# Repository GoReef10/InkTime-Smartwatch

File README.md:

# InkTime Smartwatch Project

InkTime is an open source startup focused on developing an affordable and customizable smartwatch centered around the nRF52840 SoC and e-ink display technology. This repository contains the full hardware design, including the schematic, PCB layout, and mechanical integration files required for mass production.

## Component Block Diagram

## Bill of Materials

| Device | Value | Qty | Parts | Product Link | Datasheet Link |
| --- | --- | --: | --- | --- | --- |
| NORDIC_NRF_4_NRF52840_QF | nRF52840-QIAA | 1 | U1 | [JLCPCB](https://jlcpcb.com/partdetail/NordicSemicon-NRF52840_QIAAR/C190794) | [Datasheet](https://infocenter.nordicsemi.com/pdf/nRF52840_PS_v1.9.pdf) |
| RT6160AWSC | RT6160AWSC | 1 | IC9 | [JLCPCB](https://jlcpcb.com/partdetail/RichtekTech-RT6160AWSC/C7065276) | [Datasheet](https://www.mouser.com/datasheet/2/1458/DS6160A_03-3104604.pdf) |
| BQ25180YBGR | BQ25180YBGR | 1 | IC1 | [JLCPCB](https://jlcpcb.com/partdetail/TexasInstruments-BQ25180YBGR/C3682423) | [Datasheet](https://www.ti.com/lit/ds/symlink/bq25180.pdf) |
| ESP32_C6_LIBRARY_MAX17048G+T10 | MAX17048G+T10 | 1 | U3 | [JLCPCB](https://jlcpcb.com/partdetail/MaximIntegrated-MAX17048GT10/C2682616) | [Datasheet](https://www.analog.com/media/en/technical-documentation/data-sheets/MAX17048-MAX17049.pdf) |
| DRV2605YZFR | DRV2605YZFR | 1 | IC2 | [JLCPCB](https://jlcpcb.com/partdetail/TexasInstruments-DRV2605YZFR/C81079) | [Datasheet](https://www.ti.com/lit/ds/symlink/drv2605.pdf) |
| BMA421 | BMA421 | 1 | IC3 | [JLCPCB](https://jlcpcb.com/partdetail/BoschSensortec-BMA421/C5242966) | [Datasheet](https://files.pine64.org/doc/datasheet/pinetime/BST-BMA421-FL000.pdf) |
| DMG2305UX-7 | DMG2305UX-7 | 1 | Q2 | [JLCPCB](https://jlcpcb.com/partdetail/HXYMOSFET-DMG2305UX7/C5261054) | [Datasheet](https://www.diodes.com/assets/Datasheets/DMG2305UX.pdf) |
| ESP32_C6_LIBRARY_6_SI1308EDL-T1-GE3 | SI1308EDL-T1-GE3 | 1 | Q3 | [JLCPCB](https://jlcpcb.com/partdetail/TECHPUBLIC-SI1308EDL/C7603347) | [Datasheet](https://www.vishay.com/docs/63399/si1308edl.pdf) |
| USBLC6-2SC6Y | USBLC6-2SC6Y | 1 | D3 | [JLCPCB](https://jlcpcb.com/partdetail/TECHPUBLIC-USBLC62SC6Y/C5310974) | [Datasheet](https://wmsc.lcsc.com/wmsc/upload/file/pdf/v2/lcsc/2401261525_TECH-PUBLIC-USBLC6-2SC6Y_C5310974.pdf) |
| MBR0530 | MBR0530 | 3 | D2, D4, D5 | [JLCPCB](https://jlcpcb.com/partdetail/4324765-MBR0530_F20000HF/C3757235) | [Datasheet](https://wmsc.lcsc.com/wmsc/upload/file/pdf/v2/lcsc/2205311800_Yangzhou-Yangjie-Electronic-Technology-MBR0530-F2-0000HF_C3757235.pdf) |
| KH-TYPE-C-16P_KH-TYPE-C-16P | KH-TYPE-C-16P | 1 | J4 | [JLCPCB](https://jlcpcb.com/partdetail/KH-TYPE-C-16P/C709357) | [Datasheet](https://wmsc.lcsc.com/wmsc/upload/file/pdf/v2/lcsc/2204251630_SHENZHEN-KINGHELM-Elec-KH-TYPE-C-16P_C709357.pdf) |
| 5034802400 | 503480-2400 | 1 | J1 | [JLCPCB](https://jlcpcb.com/partdetail/MOLEX-5034802400/C122434) | [Datasheet](https://www.mouser.com/datasheet/2/276/2/5034802400_FFC_FPC_CONNECTORS-1112921.pdf) |
| EVP-AKE31A | EVP-AKE31A | 3 | SW_DN, SW_ENT, SW_UP | [JLCPCB](https://jlcpcb.com/partdetail/PANASONIC-EVPAKE31A/C569760) | [Datasheet](https://www.lcsc.com/datasheet/C569760.pdf) |
| 2450AT18B100E_2450AT18B100E | 2450AT18B100E | 1 | ANT1 | [JLCPCB](https://jlcpcb.com/partdetail/JohansonTechnology-2450AT18B100/C2836414) | [Datasheet](https://www.johansontechnology.com/datasheets/antennas/2450AT18B100.pdf) |
| NX2016SA-32MHZ-STD-CZS-5 | 32 MHz | 1 | X1 | [JLCPCB](https://jlcpcb.com/partdetail/NDK-NX2016SA_32MHZ_STD_CZS5/C843260) | [Datasheet](https://www.lcsc.com/datasheet/C843260.pdf) |
| NORDIC_NRF_1_XTAL_32KHZ | 32.768 kHz | 1 | X2 | [JLCPCB](https://jlcpcb.com/partdetail/NDK-NX3215SA_32_768K_STD_MUA9/C519280) | [Datasheet](https://www.ndk.com/images/products/crystal/resonator/NX3215SA_e.pdf) |
| MLP2016SR47MT0S1_FTC252012SR47MBCA | FTC252012SR47MBCA | 1 | L7 | [JLCPCB](https://jlcpcb.com/partdetail/6763488-FTC252012SR47MBCA/C5832368) | [Datasheet](https://wmsc.lcsc.com/wmsc/upload/file/pdf/v2/lcsc/2311271530_TDK-FTC252012SR47MBCA_C5832368.pdf) |
| VHF060303H3N9ST | 3.9 nH | 1 | L1 | [JLCPCB](https://jlcpcb.com/partdetail/153834-VHF060303H3N9ST/C142503) | [Datasheet](https://www.lcsc.com/datasheet/C142503.pdf) |
| MLK0603L15NJT000 | 15 nH | 1 | L3 | [JLCPCB](https://jlcpcb.com/partdetail/TDK-MLK0603L15NJT000/C6990407) | [Datasheet](https://www.lcsc.com/datasheet/C6990407.pdf) |
| RNCF0201DTC3K30 | 3.3 kΩ | 2 | R17, R18 | [JLCPCB](https://jlcpcb.com/partdetail/SEI_Stackpole_Elec-RNCF0201DTC3K30/C2487997) | [Datasheet](https://www.lcsc.com/datasheet/C2487997.pdf) |
| RC0201FR-075K1L | 5.1 kΩ | 2 | R1_USB, R2_USB | [JLCPCB](https://jlcpcb.com/partdetail/YAGEO-RC0201FR075K1L/C274341) | [Datasheet](https://www.lcsc.com/datasheet/C274341.pdf) |
| RC0201FR-1310KL | 10 kΩ | 6 | R2_EP_DR, R5, R7, R8, R9, R_PWR_EPD | [JLCPCB](https://jlcpcb.com/partdetail/YAGEO-RC0201FR1310KL/C6373588) | [Datasheet](https://www.lcsc.com/datasheet/C6373588.pdf) |
| 0201WMF220KTCE | 2.2 Ω | 1 | R_TYPE_SEL | [JLCPCB](https://jlcpcb.com/partdetail/244650-0201WMF220KTCE/C247442) | [Datasheet](https://www.lcsc.com/datasheet/C247442.pdf) |
| 0201WMJ0000TCE | 0 Ω | 3 | R2, R3, R4 | [JLCPCB](https://jlcpcb.com/partdetail/25793-0201WMJ0000TCE/C25050) | [Datasheet](https://www.lcsc.com/datasheet/C25050.pdf) |
| MA0201XF821K250 | 820 pF | 1 | C9 | [JLCPCB](https://jlcpcb.com/partdetail/Meritek-MA0201XF821K250/C3842403) | [Datasheet](https://www.lcsc.com/datasheet/C3842403.pdf) |
| GRM0335C1E1R0CA01J | 1 pF | 2 | C3, C4 | [JLCPCB](https://jlcpcb.com/partdetail/2274979-GRM0335C1E1R0CA01J/C2182912) | [Datasheet](https://www.lcsc.com/datasheet/C2182912.pdf) |
| 0201N120J250CT | 12 pF | 4 | C1, C2, C17, C18 | [JLCPCB](https://jlcpcb.com/partdetail/Walsin_TechCorp-0201N120J250CT/C424835) | [Datasheet](https://www.lcsc.com/datasheet/C424835.pdf) |
| 0201N101F160CT | 100 pF | 1 | C11 | [JLCPCB](https://jlcpcb.com/partdetail/Walsin_TechCorp-0201N101F160CT/C3847857) | [Datasheet](https://www.lcsc.com/datasheet/C3847857.pdf) |
| C0201X5R473K160NTA | 47 nF | 1 | C16 | [JLCPCB](https://jlcpcb.com/partdetail/126083-C0201X5R473K160NTA/C124806) | [Datasheet](https://www.lcsc.com/datasheet/C124806.pdf) |
| AC0201KRX6S6BB104 | 100 nF | 9 | C5, C7, C8, C12, C19, C23, C27, C34, C42 | [JLCPCB](https://jlcpcb.com/partdetail/YAGEO-AC0201KRX6S6BB104/C3855913) | [Datasheet](https://www.lcsc.com/datasheet/C3855913.pdf) |
| CL05A105KP5NNNC | 1 uF | 1 | C15 | [JLCPCB](https://jlcpcb.com/partdetail/C14445) | [Datasheet](https://www.lcsc.com/datasheet/C14445.pdf) |
| GRM155R61H105KE05D | 1 uF / 50V | 9 | EPD_C1, EPD_C2, EPD_C6, EPD_C7, EPD_C8, EPD_C9, EPD_C10, EPD_C11, EPD_C12 | [JLCPCB](https://jlcpcb.com/partdetail/1609005-GRM155R61H105KE05D/C1518208) | [Datasheet](https://www.lcsc.com/datasheet/C1518208.pdf) |
| GRM155R61A475KEAAD | 4.7 uF | 5 | C6, C14, C20, C21, C43 | [JLCPCB](https://jlcpcb.com/partdetail/MurataElectronics-GRM155R61A475KEAAD/C77004) | [Datasheet](https://www.lcsc.com/datasheet/C77004.pdf) |
| C0402X5R475M250NT | 4.7 uF / 25V | 1 | C2-EP-DR | [JLCPCB](https://jlcpcb.com/partdetail/SANYEAR-C0402X5R475M250NT/C2911388) | [Datasheet](https://www.lcsc.com/datasheet/C2911388.pdf) |
| 0402X106M100CT | 10 uF | 2 | C24, C39 | [JLCPCB](https://jlcpcb.com/partdetail/Walsin_TechCorp-0402X106M100CT/C2992625) | [Datasheet](https://www.lcsc.com/datasheet/C2992625.pdf) |
| CL05A226MQ6ZUN8 | 22 uF | 2 | C25, C33 | [JLCPCB](https://jlcpcb.com/partdetail/2889851-CL05A226MQ6ZUN8/C2762589) | [Datasheet](https://www.lcsc.com/datasheet/C2762589.pdf) |

## Hardware Description

### Microcontroller - nRF52840 (Nordic Semiconductor)

The core of InkTime is the **nRF52840**. It manages all peripherals and runs the main firmware:

### Power System

- **LiPo Charger - BQ25180YBGR :** Single-cell Li-Ion/LiPo charger connected via **I2C**, handles charge current control and power path management.
- **DC/DC Buck-Boost - RT6160AWSC:** Provides the regulated **3.3 V rail** (VREG/3V3) from the battery, using a 10 uH inductor. Supplies the MCU and most peripherals.
- **Fuel Gauge - MAX17048G+T10:** Monitors battery state-of-charge via **I2C**, provides a `ALERT` line to the MCU for low-battery interrupts.

### E-Paper Display

The display connects through a 24-pin FPC connector (J1). The drive circuit uses:
- A boost converter to generate the higher voltages required by e-paper panels (PREVGH/PREVGL rails).
- Communication with the MCU via SPI (MOSI, SCK, CS, DC, RST, BUSY lines).

E-paper was chosen for its near-zero power draw when the display is static - only consuming power during refresh.

### IMU - BMA421

A 3-axis accelerometer connected via I2C, with two interrupt lines (`INT1`, `INT2`) wired to the MCU for step counting, wrist-tilt detection, and activity recognition without polling.

### Haptic Driver - DRV2605YZFR

Controls a vibration motor/LRA actuator. Connected via **I2C**, with an enable line (`HAPTIC_EN`) from the MCU. Supports waveform libraries for rich haptic feedback patterns.

### USB - KH-TYPE-C-16P + USBLC6-2SC6Y

Full-speed USB Type-C connector for charging and data. The USBLC6-2SC6Y provides ESD protection on D+/D− lines. CC1/CC2 resistors (5.1 kΩ) handle cable orientation detection. VBUS is routed to the LiPo charger.

### Buttons

Three tactile buttons (UP, DOWN, ENTER) with pull-up resistors, directly connected to GPIO pins.

### Debug Interface - TC2030-IDC (Tag-Connect)

A 6-pin **SWD** debug/programming header (SWDCLK, SWDIO, RESET, SWO, 3.3V, GND) for firmware flashing and debugging, with test points exposed for each signal.

## nRF52840 Pin Assignment - InkTime v5

### SPI - E-Paper Display
| Pin | Function | Why |
|-----|----------|-----|
| P0.08 | MOSI | SPI data out to EPD controller |
| P0.11 | SCK | SPI clock |
| P0.13 | EPD_CS | Chip select - activates the display |
| P0.14 | EPD_DC | Data/Command toggle for EPD protocol |
| P1.01 | EPD_RST | Hardware reset of the display controller |
| P1.02 | EPD_BUSY | Polled input - MCU waits for display to finish refreshing |

### I2C - Shared Bus (BQ25180, MAX17048, BMA421, DRV2605)
| Pin | Function | Why |
|-----|----------|-----|
| P0.26 | SCL | I2C clock, shared by all 4 peripherals |
| P0.27 | SDA | I2C data, shared by all 4 peripherals |

### Interrupts & Control
| Pin | Function | Why |
|-----|----------|-----|
| P0.04 | PMIC_INT | BQ25180 interrupt - charge events (fault, complete, etc.) |
| P1.09 | ALERT | MAX17048 interrupt - low battery or 1% SoC change |
| P0.25 | IMU_INT1 | BMA421 primary interrupt - step count, wakeup-on-motion |
| P0.24 | IMU_INT2 | BMA421 secondary interrupt - activity recognition events |
| P1.01 | HAPTIC_EN | Enables DRV2605 and triggers haptic waveform playback |

### Buttons
| Pin | Function | Why |
|-----|----------|-----|
| P0.29 | SW_UP | Up button - GPIOTE falling-edge interrupt, also wakes MCU from sleep |
| P0.30 | SW_DN | Down button - same as above |
| P0.31 | SW_ENT | Enter button - same as above |

### USB
| Pin | Function | Why |
|-----|----------|-----|
| D+ | USB D+ | Native USB 2.0 FS controller - firmware updates, serial debug |
| D− | USB D− | Paired with D+ |
| VBUS | USB power detect | MCU detects cable insertion to enable charging path |

### Crystal Oscillators
| Pin | Function | Why |
|-----|----------|-----|
| XL1 / XL2 | 32.768 kHz XTAL | Low-frequency RTC clock - timekeeping during deep sleep |
| XC1 / XC2 | 32 MHz XTAL | Main system clock for CPU and radio |

### SWD Debug
| Pin | Function | Why |
|-----|----------|-----|
| SWDCLK | SWD clock | Firmware flashing and live debugging via Tag-Connect |
| SWDIO | SWD data | Bidirectional debug data |
| P1.00 | SWO | Serial Wire Output - trace/printf during development |
| P0.18 | RESET | Hardware reset, also accessible on debug header |

### RF
| Pin | Function | Why |
|-----|----------|-----|
| ANT | 2.4 GHz antenna | Connected via LC matching network to the onboard ceramic antenna |
| VSS_PA | PA ground | Dedicated quiet ground for the RF power amplifier |

## Design Log

### Silkscreen
Silkscreen line width was set to **0.9 mm**, reduced to **0.8 mm** in areas where overlap with component courtyard or pad holes would otherwise occur. While the standard recommendation is 1 mm, 0.9 mm remains legible after fabrication. To reduce visual clutter, silkscreen labels were kept only for functionally important components (ICs, connectors, test points) - passive components such as resistors and capacitors were left unlabeled.

### Test Points
All test points (SWD signals, power rails, I2C lines) were placed close to the board edge to allow easy probing during bring-up and testing without needing to reach into the center of the board.

### Antenna Placement
The BLE antenna (2450AT18B100E) was placed at the edge of the PCB, away from other components and copper fills, to minimize RF interference and avoid detuning the antenna due to nearby conductors - a standard requirement for 2.4 GHz PCB antennas.

### Trace Width & Clearance
Power traces were routed at 0.3 mm as per design requirements. In a small number of cases, traces were temporarily narrowed immediately at component pins due to clearance constraints, then returned to 0.3 mm as soon as space allowed. This was done only where unavoidable and over very short distances, keeping the resistive impact negligible.

### 2-Layer Stackup
A 2-layer board (top + bottom copper) was chosen deliberately as the design complexity is manageable within 2 layers, so the added cost of additional layers would bring no practical benefit.

Power traces were routed on the top layer. The only exception is a short segment of the **3V3 trace** which briefly routes through the bottom layer through 3 vias, due to a localized routing constraint. This was kept to an absolute minimum, which is particularly important for noisy nets like the e-paper boost converter output.

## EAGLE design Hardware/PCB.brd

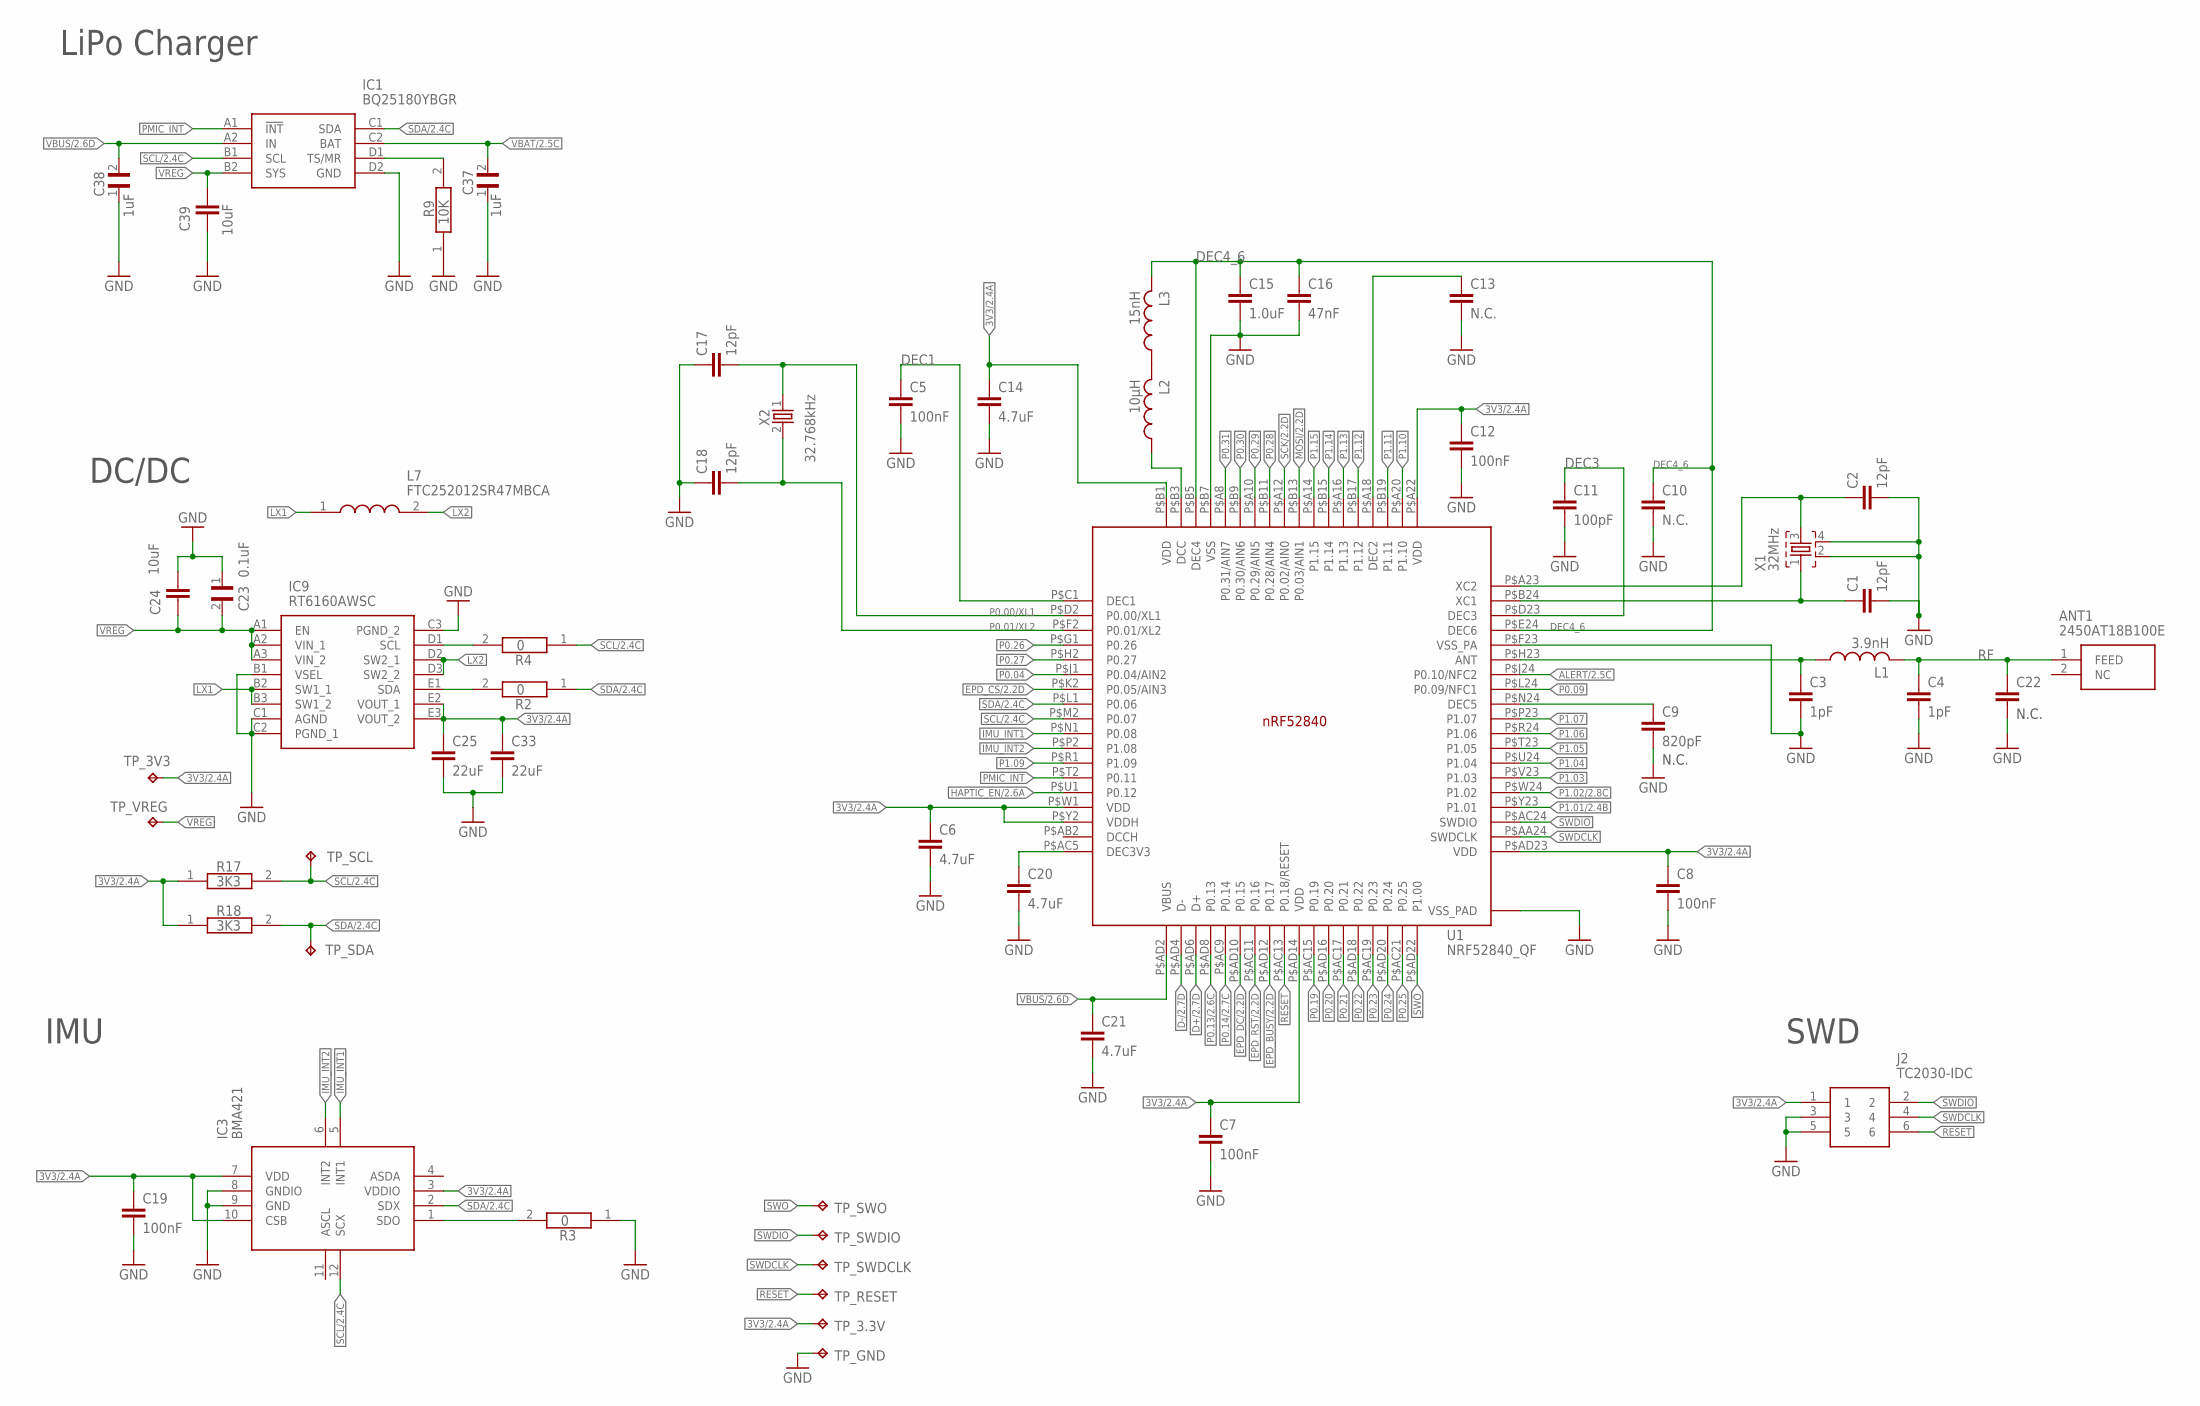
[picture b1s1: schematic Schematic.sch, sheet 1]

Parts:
ANT1: 2450AT18B100E; 2450AT18B100E_ANTC3216X140N
C1, C2, C17, C18: 12pF; NORDIC_NRF_3_RESC0201_L
C3, C4: 1pF; NORDIC_NRF_3_RESC0201_L
C5, C7, C8, C12, C19: 100nF; NORDIC_NRF_3_RESC0201_L
C6, C14, C20, C21: 4.7uF; NORDIC_NRF_3_RESC0402_L
C9: 820pF; NORDIC_NRF_3_RESC0201_L
C10, C13, C22: N.C.; NORDIC_NRF_3_RESC0201_L
C11: 100pF; NORDIC_NRF_3_RESC0201_L
C15: 1.0uF; NORDIC_NRF_3_RESC0402_L
C16: 47nF; NORDIC_NRF_3_RESC0201_L
C23: 0.1uF; GRM011R60J152KE01L_1_0201
C24, C39: 10uF; NORDIC_NRF_3_RESC0402_L
C25, C33: 22uF; NORDIC_NRF_3_RESC0402_L
C37, C38: 1uF; GRM011R60J152KE01L_1_0201
IC1: BQ25180YBGR; BQ25180YBGR_BGA8C40P2X4_100X155X50
IC3: BMA421; BMA423_BMA423
IC9: RT6160AWSC; RT6160AWSC_BGA15C40P3X5_140X230X60
J2: TC2030-IDC; TC2030-IDC_TC2030IDC
L1: 3.9nH; NORDIC_NRF_2_RESC0402_L
L2: 10μH; NORDIC_NRF_2_RESC0402_L
L3: 15nH; NORDIC_NRF_2_RESC0402_L
L7: FTC252012SR47MBCA; MLP2016SR47MT0S1_INDC2016X100N
R2, R3, R4: 0; ERA-1AEB3401C_0201
R9: 10K; ERA-1AEB3401C_0201
R17, R18: 3K3; ERA-1AEB3401C_0201
TP_3.3V, TP_3V3: HECTOR_WATCH_1_TPTP20R; HECTOR_WATCH_1_TP20R
TP_GND: HECTOR_WATCH_1_TPTP20R; HECTOR_WATCH_1_TP20R
TP_RESET: HECTOR_WATCH_1_TPTP20R; HECTOR_WATCH_1_TP20R
TP_SCL: HECTOR_WATCH_1_TPTP20R; HECTOR_WATCH_1_TP20R
TP_SDA: HECTOR_WATCH_1_TPTP20R; HECTOR_WATCH_1_TP20R
TP_SWDCLK: HECTOR_WATCH_1_TPTP20R; HECTOR_WATCH_1_TP20R
TP_SWDIO: HECTOR_WATCH_1_TPTP20R; HECTOR_WATCH_1_TP20R
TP_SWO: HECTOR_WATCH_1_TPTP20R; HECTOR_WATCH_1_TP20R
TP_VREG: HECTOR_WATCH_1_TPTP20R; HECTOR_WATCH_1_TP20R
U1: NRF52840_QF; NORDIC_NRF_4_AQFN50P700X700X85_HS-74N
X1: 32MHz; NORDIC_NRF_BT-XTAL_2016_N
X2: 32.768kHz; NORDIC_NRF_1_XTAL_3215_N

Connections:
3V3/2.4A: C6.1, C7.1, C8.1, C12.1, C14.1, C19.1, C25.1, C33.1, IC3.3 (VDDIO), IC3.7 (VDD), IC3.10 (CSB), IC9.E2 (VOUT_1), IC9.E3 (VOUT_2), J2.1, R17.1, R18.1, TP_3.3V.TP, TP_3V3.TP, U1.P$A22 (VDD), U1.P$AD14 (VDD), U1.P$AD23 (VDD), U1.P$B1 (VDD), U1.P$W1 (VDD), U1.P$Y2 (VDDH)
ALERT/2.5C: U1.P$J24 (P0.10/NFC2)
D+/2.7D: U1.P$AD6 (D+)
D-/2.7D: U1.P$AD4 (D-)
DEC1: C5.1, U1.P$C1 (DEC1)
DEC3: C11.1, U1.P$D23 (DEC3)
DEC4_6: C10.1, C15.1, C16.1, L3.2, U1.P$B5 (DEC4), U1.P$E24 (DEC6)
EPD_BUSY/2.2D: U1.P$AD12 (P0.17)
EPD_CS/2.2D: U1.P$K2 (P0.05/AIN3)
EPD_DC/2.2D: U1.P$AD10 (P0.15)
EPD_RST/2.2D: U1.P$AC11 (P0.16)
GND: C1.2, C2.2, C3.2, C4.2, C5.2, C6.2, C7.2, C8.2, C9.2, C10.2, C11.2, C12.2, C13.2, C14.2, C15.2, C16.2, C17.1, C18.1, C19.2, C20.2, C21.2, C22.2, C23.1, C24.1, C25.2, C33.2, C37.1, C38.1, C39.2, IC1.D2 (GND), IC3.8 (GNDIO), IC3.9 (GND), IC9.B1 (VSEL), IC9.C1 (AGND), IC9.C2 (PGND_1), IC9.C3 (PGND_2), J2.3, J2.5, R3.1, R9.1, TP_GND.TP, U1.P$74 (VSS_PAD), U1.P$75 (VSS_PAD), U1.P$76 (VSS_PAD), U1.P$77 (VSS_PAD), U1.P$78 (VSS_PAD), U1.P$79 (VSS_PAD), U1.P$80 (VSS_PAD), U1.P$81 (VSS_PAD), U1.P$82 (VSS_PAD), U1.P$83 (VSS_PAD), U1.P$84 (VSS_PAD), U1.P$85 (VSS_PAD), U1.P$86 (VSS_PAD), U1.P$87 (VSS_PAD), U1.P$88 (VSS_PAD), U1.P$89 (VSS_PAD), U1.P$90 (VSS_PAD), U1.P$B7 (VSS), U1.P$F23 (VSS_PA), X1.2, X1.4; also elsewhere on the board
HAPTIC_EN/2.6A: U1.P$U1 (P0.12)
IMU_INT1: IC3.5 (INT1), U1.P$N1 (P0.08)
IMU_INT2: IC3.6 (INT2), U1.P$P2 (P1.08)
LX1: IC9.B2 (SW1_1), IC9.B3 (SW1_2), L7.1
LX2: IC9.D2 (SW2_1), IC9.D3 (SW2_2), L7.2
MOSI/2.2D: U1.P$B13 (P0.03/AIN1)
unnamed: C20.1, U1.P$AC5 (DEC3V3)
unnamed: L2.2, L3.1
unnamed: L2.1, U1.P$B3 (DCC)
unnamed: C1.1, U1.P$B24 (XC1), X1.1
unnamed: C2.1, U1.P$A23 (XC2), X1.3
unnamed: IC9.E1 (SDA), R2.2
unnamed: IC9.D1 (SCL), R4.2
unnamed: IC1.D1 (TS/MR), R9.2
unnamed: C13.1, U1.P$A18 (DEC2)
unnamed: C9.1, U1.P$N24 (DEC5)
unnamed: IC3.1 (SDO), R3.2
unnamed: C3.1, L1.1, U1.P$H23 (ANT)
P0.00/XL1: C17.2, U1.P$D2 (P0.00/XL1), X2.1
P0.01/XL2: C18.2, U1.P$F2 (P0.01/XL2), X2.2
P0.04: U1.P$J1 (P0.04/AIN2)
P0.09: U1.P$L24 (P0.09/NFC1)
P0.13/2.6C: U1.P$AD8 (P0.13)
P0.14/2.7C: U1.P$AC9 (P0.14)
P0.19: U1.P$AC15 (P0.19)
P0.20: U1.P$AD16 (P0.20)
P0.21: U1.P$AC17 (P0.21)
P0.22: U1.P$AD18 (P0.22)
P0.23: U1.P$AC19 (P0.23)
P0.24: U1.P$AD20 (P0.24)
P0.25: U1.P$AC21 (P0.25)
P0.26: U1.P$G1 (P0.26)
P0.27: U1.P$H2 (P0.27)
P0.28: U1.P$B11 (P0.28/AIN4)
P0.29: U1.P$A10 (P0.29/AIN5)
P0.30: U1.P$B9 (P0.30/AIN6)
P0.31: U1.P$A8 (P0.31/AIN7)
P1.01/2.4B: U1.P$Y23 (P1.01)
P1.02/2.8C: U1.P$W24 (P1.02)
P1.03: U1.P$V23 (P1.03)
P1.04: U1.P$U24 (P1.04)
P1.05: U1.P$T23 (P1.05)
P1.06: U1.P$R24 (P1.06)
P1.07: U1.P$P23 (P1.07)
P1.09: U1.P$R1 (P1.09)
P1.10: U1.P$A20 (P1.10)
P1.11: U1.P$B19 (P1.11)
P1.12: U1.P$B17 (P1.12)
P1.13: U1.P$A16 (P1.13)
P1.14: U1.P$B15 (P1.14)
P1.15: U1.P$A14 (P1.15)
PMIC_INT: IC1.A1 (!INT), U1.P$T2 (P0.11)
RESET: J2.6, TP_RESET.TP, U1.P$AC13 (P0.18/RESET)
RF: ANT1.1 (FEED), C4.1, C22.1, L1.2
SCK/2.2D: U1.P$A12 (P0.02/AIN0)
SCL/2.4C: IC1.B1 (SCL), IC3.12 (SCX), R4.1, R17.2, TP_SCL.TP, U1.P$M2 (P0.07)
SDA/2.4C: IC1.C1 (SDA), IC3.2 (SDX), R2.1, R18.2, TP_SDA.TP, U1.P$L1 (P0.06)
SWDCLK: J2.4, TP_SWDCLK.TP, U1.P$AA24 (SWDCLK)
SWDIO: J2.2, TP_SWDIO.TP, U1.P$AC24 (SWDIO)
SWO: TP_SWO.TP, U1.P$AD22 (P1.00)
VBAT/2.5C: C37.2, IC1.C2 (BAT)
VBUS/2.6D: C21.1, C38.2, IC1.A2 (IN), U1.P$AD2 (VBUS)
VREG: C23.2, C24.2, C39.1, IC1.B2 (SYS), IC9.A1 (EN), IC9.A2 (VIN_1), IC9.A3 (VIN_2), TP_VREG.TP

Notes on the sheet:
LiPo Charger
DC/DC
IMU
SWD
N.C.

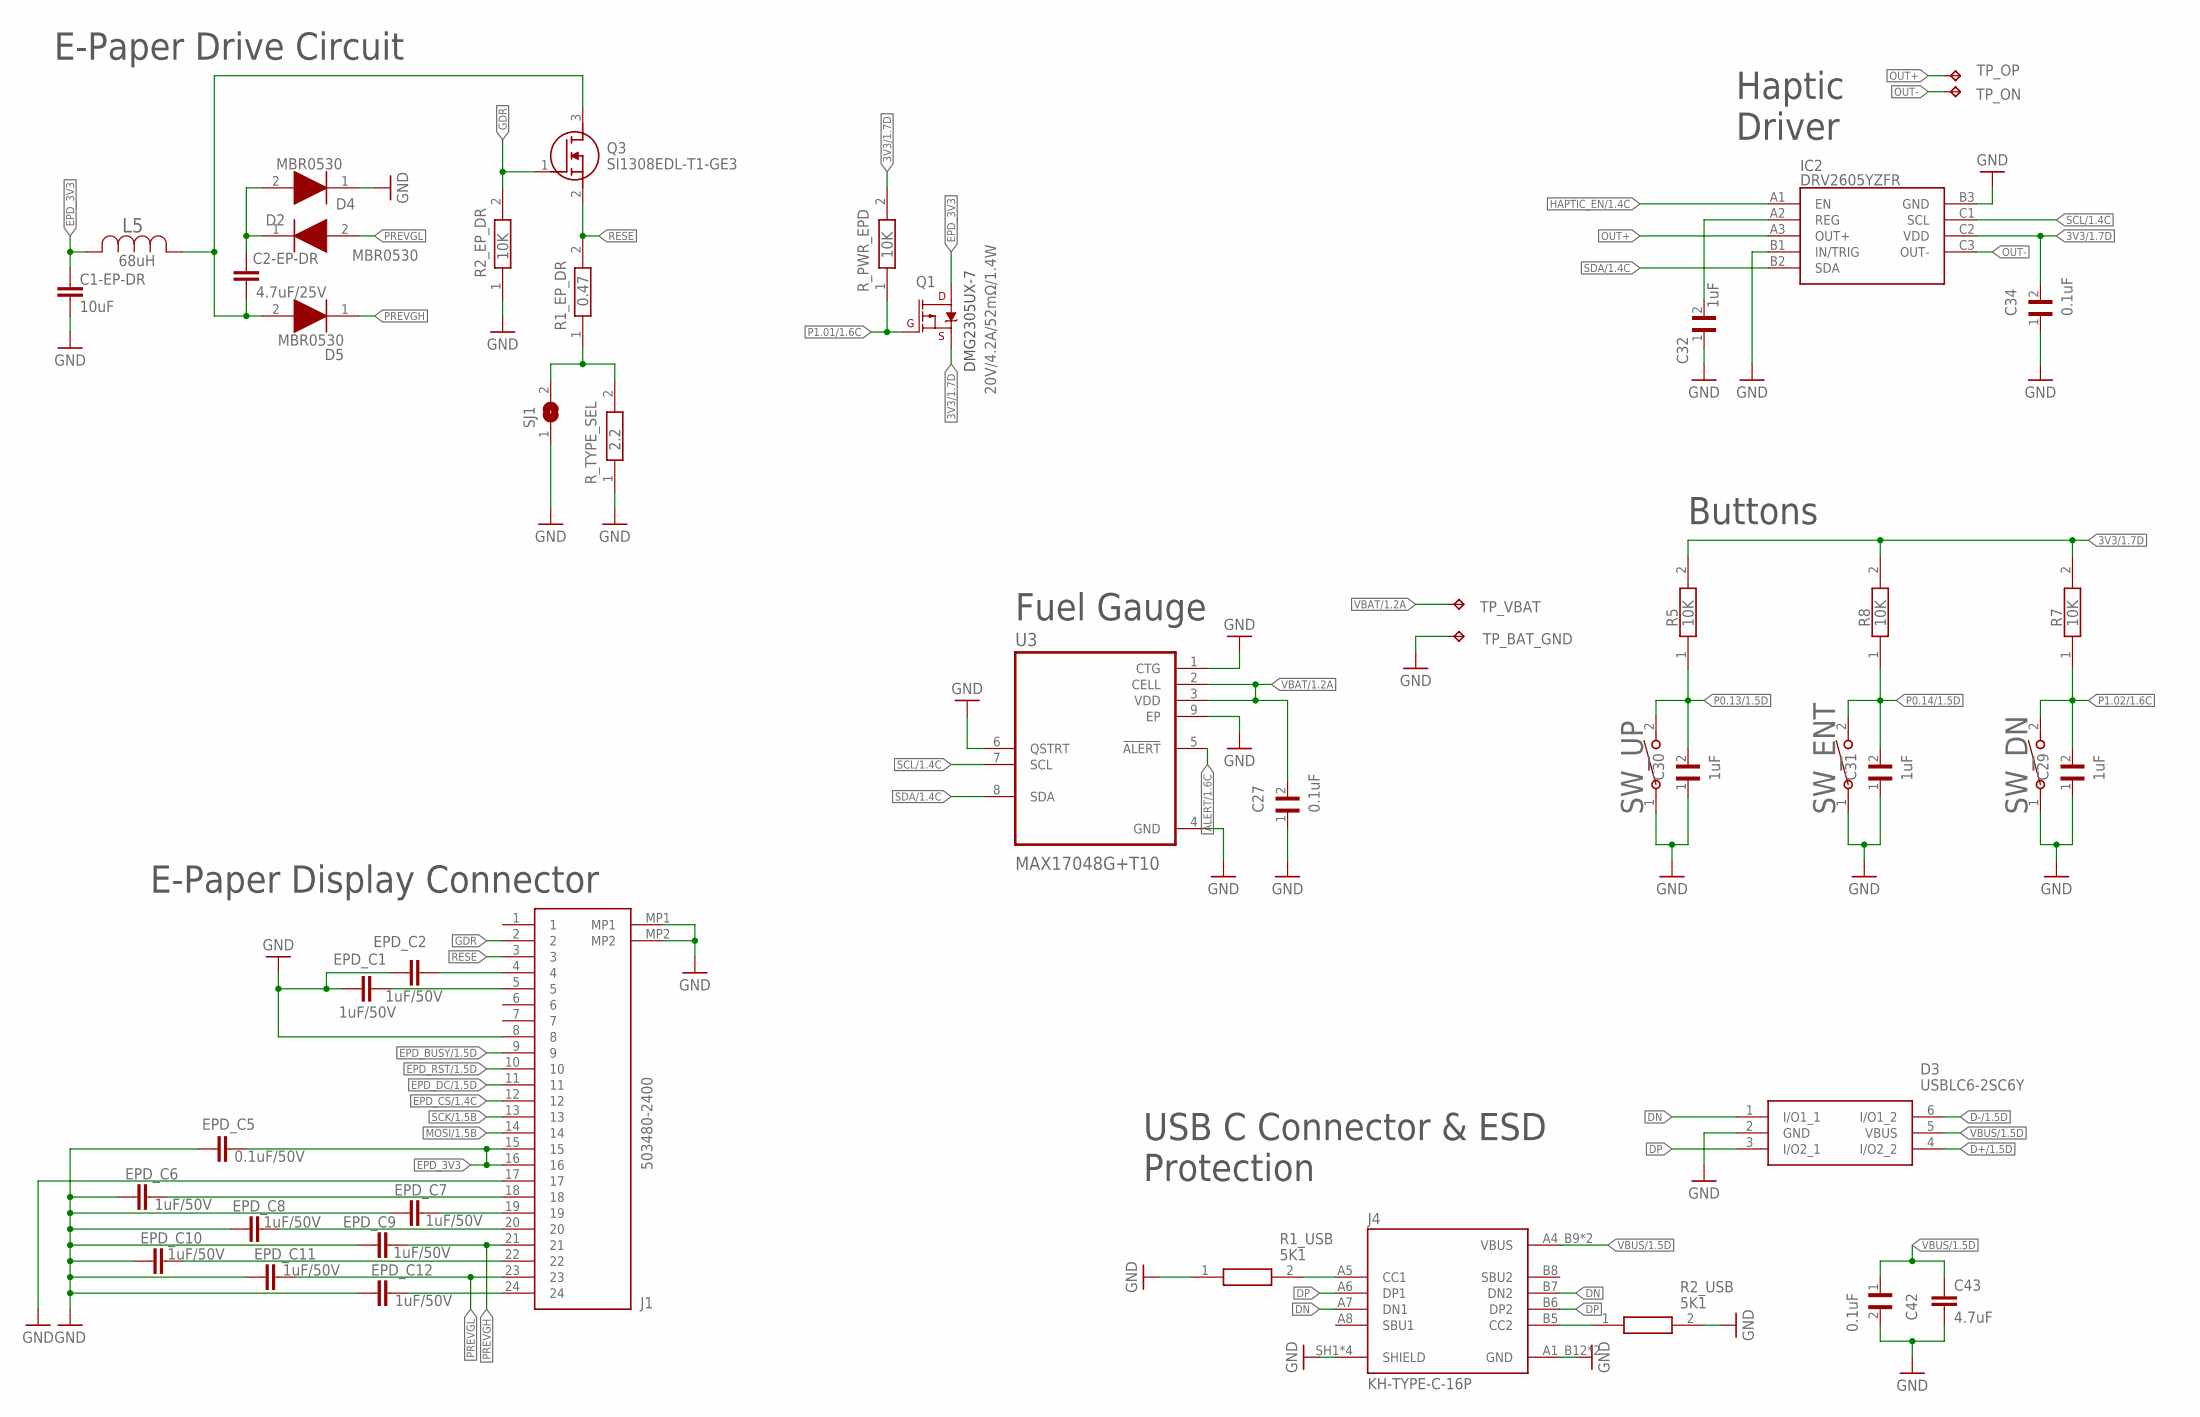
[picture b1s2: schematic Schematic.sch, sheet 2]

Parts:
C1-EP-DR: 10uF; NORDIC_NRF_3_RESC0402_L
C2-EP-DR: 4.7uF/25V; NORDIC_NRF_3_RESC0402_L
C27, C34, C42: 0.1uF; GRM011R60J152KE01L_1_0201
C29, C30, C31, C32: 1uF; GRM011R60J152KE01L_1_0201
C43: 4.7uF; NORDIC_NRF_3_RESC0402_L
D2, D4, D5: MBR0530; ESP32_C6_LIBRARY_5_SOD3716X135N
D3: USBLC6-2SC6Y; ESP32_C6_LIBRARY_3_SOT95P280X145-6N
EPD_C1, EPD_C2, EPD_C6, EPD_C7, EPD_C8, EPD_C9, EPD_C10, EPD_C11, EPD_C12: 1uF/50V; NORDIC_NRF_3_RESC0402_L
EPD_C5: 0.1uF/50V; NORDIC_NRF_3_RESC0201_L
IC2: DRV2605YZFR; DRV2605YZFR_BGA9C50P3X3_144X144X62
J1: 503480-2400; 503480-2400_5034802400
J4: KH-TYPE-C-16P; KH-TYPE-C-16P_KINGHELM_KH-TYPE-C-16P
L5: 68uH; ESP32_C6_LIBRARY_2_IND_4828-WE-TPC_WRE
Q1: 20V/4.2A/52mΩ/1.4W; ESP32_C6_LIBRARY_4_ESP32_C6_LIBRARY_4_ESP32_C6_LIBRARY_4_ES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
Q3: SI1308EDL-T1-GE3; ESP32_C6_LIBRARY_6_SOT65P210X110-3N
R1_EP_DR: 0.47; ERA-1AEB3401C_0201
R1_USB, R2_USB: 5K1; ERA-1AEB3401C_0201
R2_EP_DR, R5, R7, R8: 10K; ERA-1AEB3401C_0201
R_PWR_EPD: 10K; ERA-1AEB3401C_0201
R_TYPE_SEL: 2.2; ERA-1AEB3401C_0201
SJ1: ESP32_C6_LIBRARY_7_JUMPER_SJ
SW_DN: 2025-10-22_07-23-44_LIBRARY_EVP-AKE31ASW_EVP-AKE3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; 2025-10-22_07-23-44_LIBRARY_SW_EVP-AKE31A_PAN
SW_ENT: 2025-10-22_07-23-44_LIBRARY_EVP-AKE31ASW_EVP-AKE3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; 2025-10-22_07-23-44_LIBRARY_SW_EVP-AKE31A_PAN
SW_UP: 2025-10-22_07-23-44_LIBRARY_EVP-AKE31ASW_EVP-AKE3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; 2025-10-22_07-23-44_LIBRARY_SW_EVP-AKE31A_PAN
TP_BAT_GND: HECTOR_WATCH_1_TPTP20R; HECTOR_WATCH_1_TP20R
TP_ON: HECTOR_WATCH_1_TPTP20R; HECTOR_WATCH_1_TP20R
TP_OP: HECTOR_WATCH_1_TPTP20R; HECTOR_WATCH_1_TP20R
TP_VBAT: HECTOR_WATCH_1_TPTP20R; HECTOR_WATCH_1_TP20R
U3: MAX17048G+T10; ESP32_C6_LIBRARY_SON50P200X200X80-9N

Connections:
3V3/1.7D: C34.2, IC2.C2 (VDD), Q1.2 (S), R5.2, R7.2, R8.2, R_PWR_EPD.2
ALERT/1.6C: U3.5 (!ALERT)
D+/1.5D: D3.4 (I/O2_2)
D-/1.5D: D3.6 (I/O1_2)
DN: D3.1 (I/O1_1), J4.A7 (DN1), J4.B7 (DN2)
DP: D3.3 (I/O2_1), J4.A6 (DP1), J4.B6 (DP2)
EPD_3V3: C1-EP-DR.2, EPD_C5.2, J1.15, J1.16, L5.2, Q1.3 (D)
EPD_BUSY/1.5D: J1.9
EPD_CS/1.4C: J1.12
EPD_DC/1.5D: J1.11
EPD_RST/1.5D: J1.10
GDR: J1.2, Q3.1 (G), R2_EP_DR.2
GND: C1-EP-DR.1, C27.1, C29.1, C30.1, C31.1, C32.1, C34.1, C42.2, C43.1, D3.2 (GND), D4.1 (K), EPD_C1.1, EPD_C2.1, EPD_C5.1, EPD_C6.1, EPD_C7.1, EPD_C8.1, EPD_C9.1, EPD_C10.1, EPD_C11.1, EPD_C12.1, IC2.B1 (IN/TRIG), IC2.B3 (GND), J1.8, J1.17, J1.MP1, J1.MP2, J4.A1_B12 (GND), J4.A12_B1 (GND), J4.SH1 (SHIELD), J4.SH2 (SHIELD), J4.SH3 (SHIELD), J4.SH4 (SHIELD), R1_USB.1, R2_EP_DR.1, R2_USB.2, R_TYPE_SEL.1, SJ1.1, SW_DN.1, SW_ENT.1, SW_UP.1, TP_BAT_GND.TP, U3.1 (CTG), U3.4 (GND), U3.6 (QSTRT), U3.9 (EP); also elsewhere on the board
HAPTIC_EN/1.4C: IC2.A1 (EN)
MOSI/1.5B: J1.14
unnamed: EPD_C12.2, J1.24
unnamed: C32.2, IC2.A2 (REG)
unnamed: R1_EP_DR.1, R_TYPE_SEL.2, SJ1.2
unnamed: EPD_C10.2, J1.22
unnamed: EPD_C8.2, J1.20
unnamed: EPD_C7.2, J1.19
unnamed: EPD_C6.2, J1.18
unnamed: C2-EP-DR.1, D5.2 (A), L5.1, Q3.3 (D)
unnamed: C2-EP-DR.2, D2.1 (K), D4.2 (A)
unnamed: J4.B5 (CC2), R2_USB.1
unnamed: EPD_C2.2, J1.4
unnamed: EPD_C1.2, J1.5
unnamed: J4.A5 (CC1), R1_USB.2
OUT+: IC2.A3 (OUT+), TP_OP.TP
OUT-: IC2.C3 (OUT-), TP_ON.TP
P0.13/1.5D: C30.2, R5.1, SW_UP.2
P0.14/1.5D: C31.2, R8.1, SW_ENT.2
P1.01/1.6C: Q1.1 (G), R_PWR_EPD.1
P1.02/1.6C: C29.2, R7.1, SW_DN.2
PREVGH: D5.1 (K), EPD_C9.2, J1.21
PREVGL: D2.2 (A), EPD_C11.2, J1.23
RESE: J1.3, Q3.2 (S), R1_EP_DR.2
SCK/1.5B: J1.13
SCL/1.4C: IC2.C1 (SCL), U3.7 (SCL)
SDA/1.4C: IC2.B2 (SDA), U3.8 (SDA)
VBAT/1.2A: C27.2, TP_VBAT.TP, U3.2 (CELL), U3.3 (VDD)
VBUS/1.5D: C42.1, C43.2, D3.5 (VBUS), J4.A4_B9 (VBUS), J4.A9_B4 (VBUS)

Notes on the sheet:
E-Paper Display Connector
E-Paper Drive Circuit
Haptic Driver
Fuel Gauge
Buttons
USB C Connector & ESD Protection
DMG2305UX-7

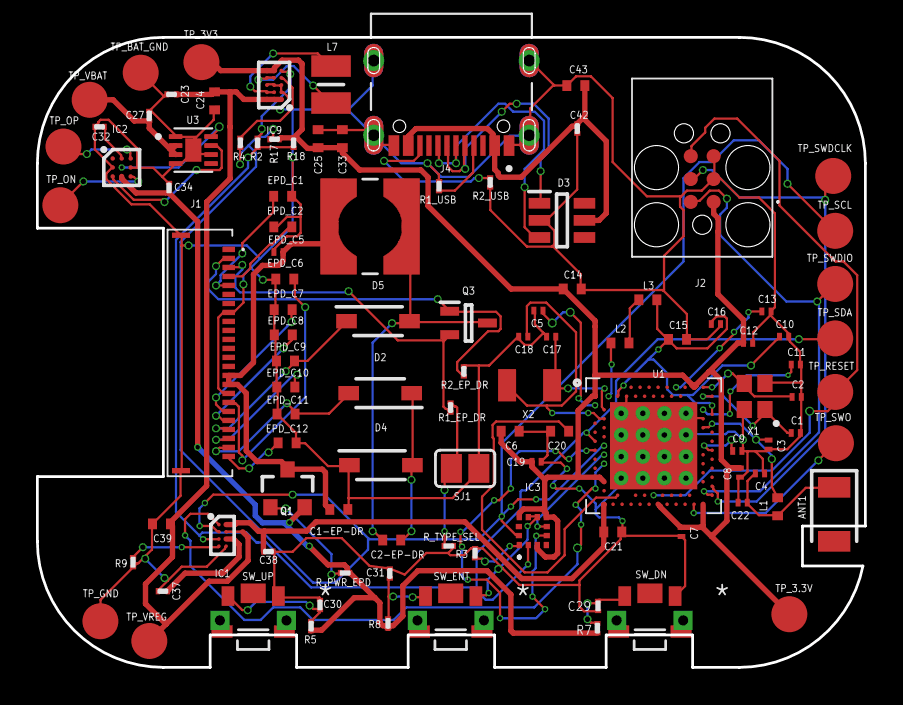
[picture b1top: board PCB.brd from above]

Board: 2 copper layers, 46.0 x 35.0 mm, 105 parts (0 on the bottom side), 65 nets.

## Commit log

2026-04-10 readme v1
2026-04-19 modify readme

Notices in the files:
parts and their libraries:
COPYRIGHT: Copyright (C) 2024 Ultra Librarian. All rights reserved.
COPYRIGHT: Copyright (C) 2025 Ultra Librarian. All rights reserved.
